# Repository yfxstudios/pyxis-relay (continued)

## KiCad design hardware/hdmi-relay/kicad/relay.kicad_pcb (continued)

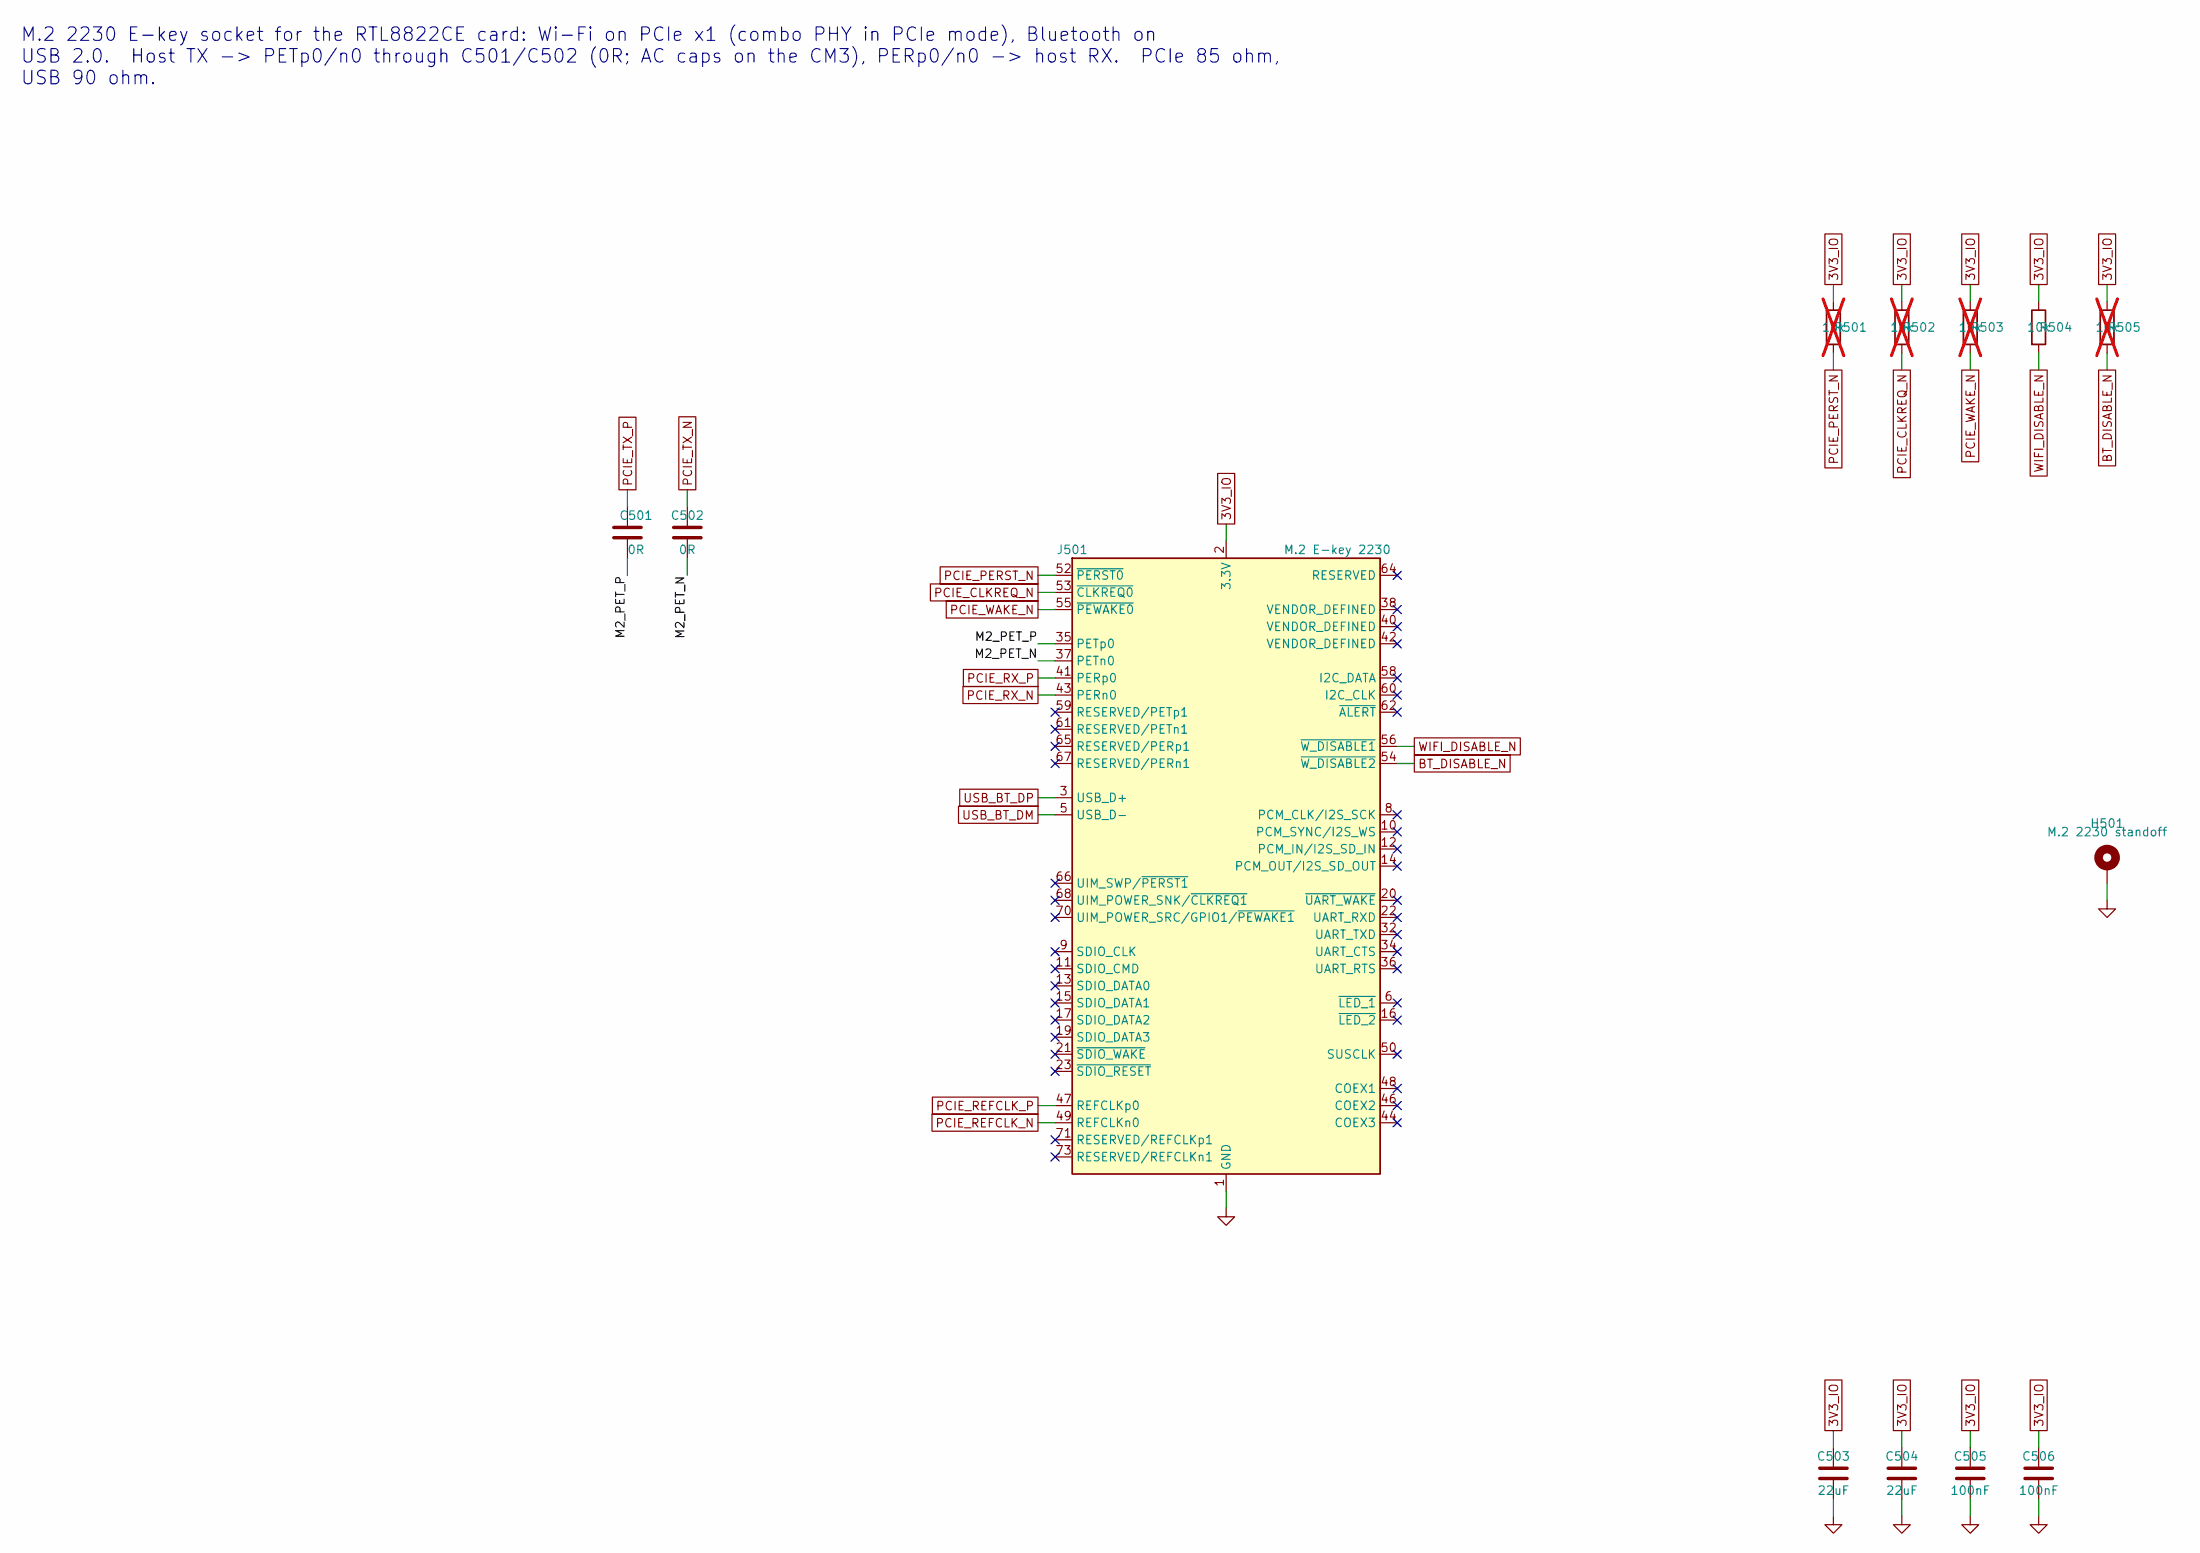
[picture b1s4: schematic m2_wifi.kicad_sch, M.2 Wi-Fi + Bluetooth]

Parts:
C501, C502: 0R; C_0402_1005Metric
C503, C504: 22uF; C_0805_2012Metric
C505, C506: 100nF; C_0402_1005Metric
H501: M.2 2230 standoff; MountingHole_2.2mm_M2_Pad_Via
J501: M.2 E-key 2230; TE_M.2_E_2x38-1MP_P0.5mm
R501, R502, R503, R505: 10k; R_0402_1005Metric; not fitted
R504: 10k; R_0402_1005Metric

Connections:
3V3_IO: C503.1, C504.1, C505.1, C506.1, J501.2 (3.3V), J501.4 (3.3V), J501.72 (3.3V), J501.74 (3.3V), R501.1, R502.1, R503.1, R504.1, R505.1; also elsewhere on the board
/M.2 Wi-Fi + Bluetooth/M2_PET_N: C502.2, J501.37 (PETn0)
/M.2 Wi-Fi + Bluetooth/M2_PET_P: C501.2, J501.35 (PETp0)
BT_DISABLE_N: J501.54 (~W_DISABLE2), R505.2; also elsewhere on the board
GND: C503.2, C504.2, C505.2, C506.2, H501.1, J501.1 (GND), J501.7 (GND), J501.18 (GND), J501.33 (GND), J501.39 (GND), J501.45 (GND), J501.51 (GND), J501.57 (GND), J501.63 (GND), J501.69 (GND), J501.75 (GND); also elsewhere on the board
PCIE_CLKREQ_N: J501.53 (~CLKREQ0), R502.2; also elsewhere on the board
PCIE_PERST_N: J501.52 (~PERST0), R501.2; also elsewhere on the board
PCIE_REFCLK_N: J501.49 (REFCLKn0); also elsewhere on the board
PCIE_REFCLK_P: J501.47 (REFCLKp0); also elsewhere on the board
PCIE_RX_N: J501.43 (PERn0); also elsewhere on the board
PCIE_RX_P: J501.41 (PERp0); also elsewhere on the board
PCIE_TX_N: C502.1; also elsewhere on the board
PCIE_TX_P: C501.1; also elsewhere on the board
PCIE_WAKE_N: J501.55 (~PEWAKE0), R503.2; also elsewhere on the board
USB_BT_DM: J501.5 (USB_D-); also elsewhere on the board
USB_BT_DP: J501.3 (USB_D+); also elsewhere on the board
WIFI_DISABLE_N: J501.56 (~W_DISABLE1), R504.2; also elsewhere on the board

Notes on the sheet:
M.2 2230 E-key socket for the RTL8822CE card: Wi-Fi on PCIe x1 (combo PHY in PCIe mode), Bluetooth on USB 2.0. Host TX -> PETp0/n0 through C501/C502 (0R; AC caps on the CM3), PERp0/n0 -> host RX. PCIe 85 ohm, USB 90 ohm.

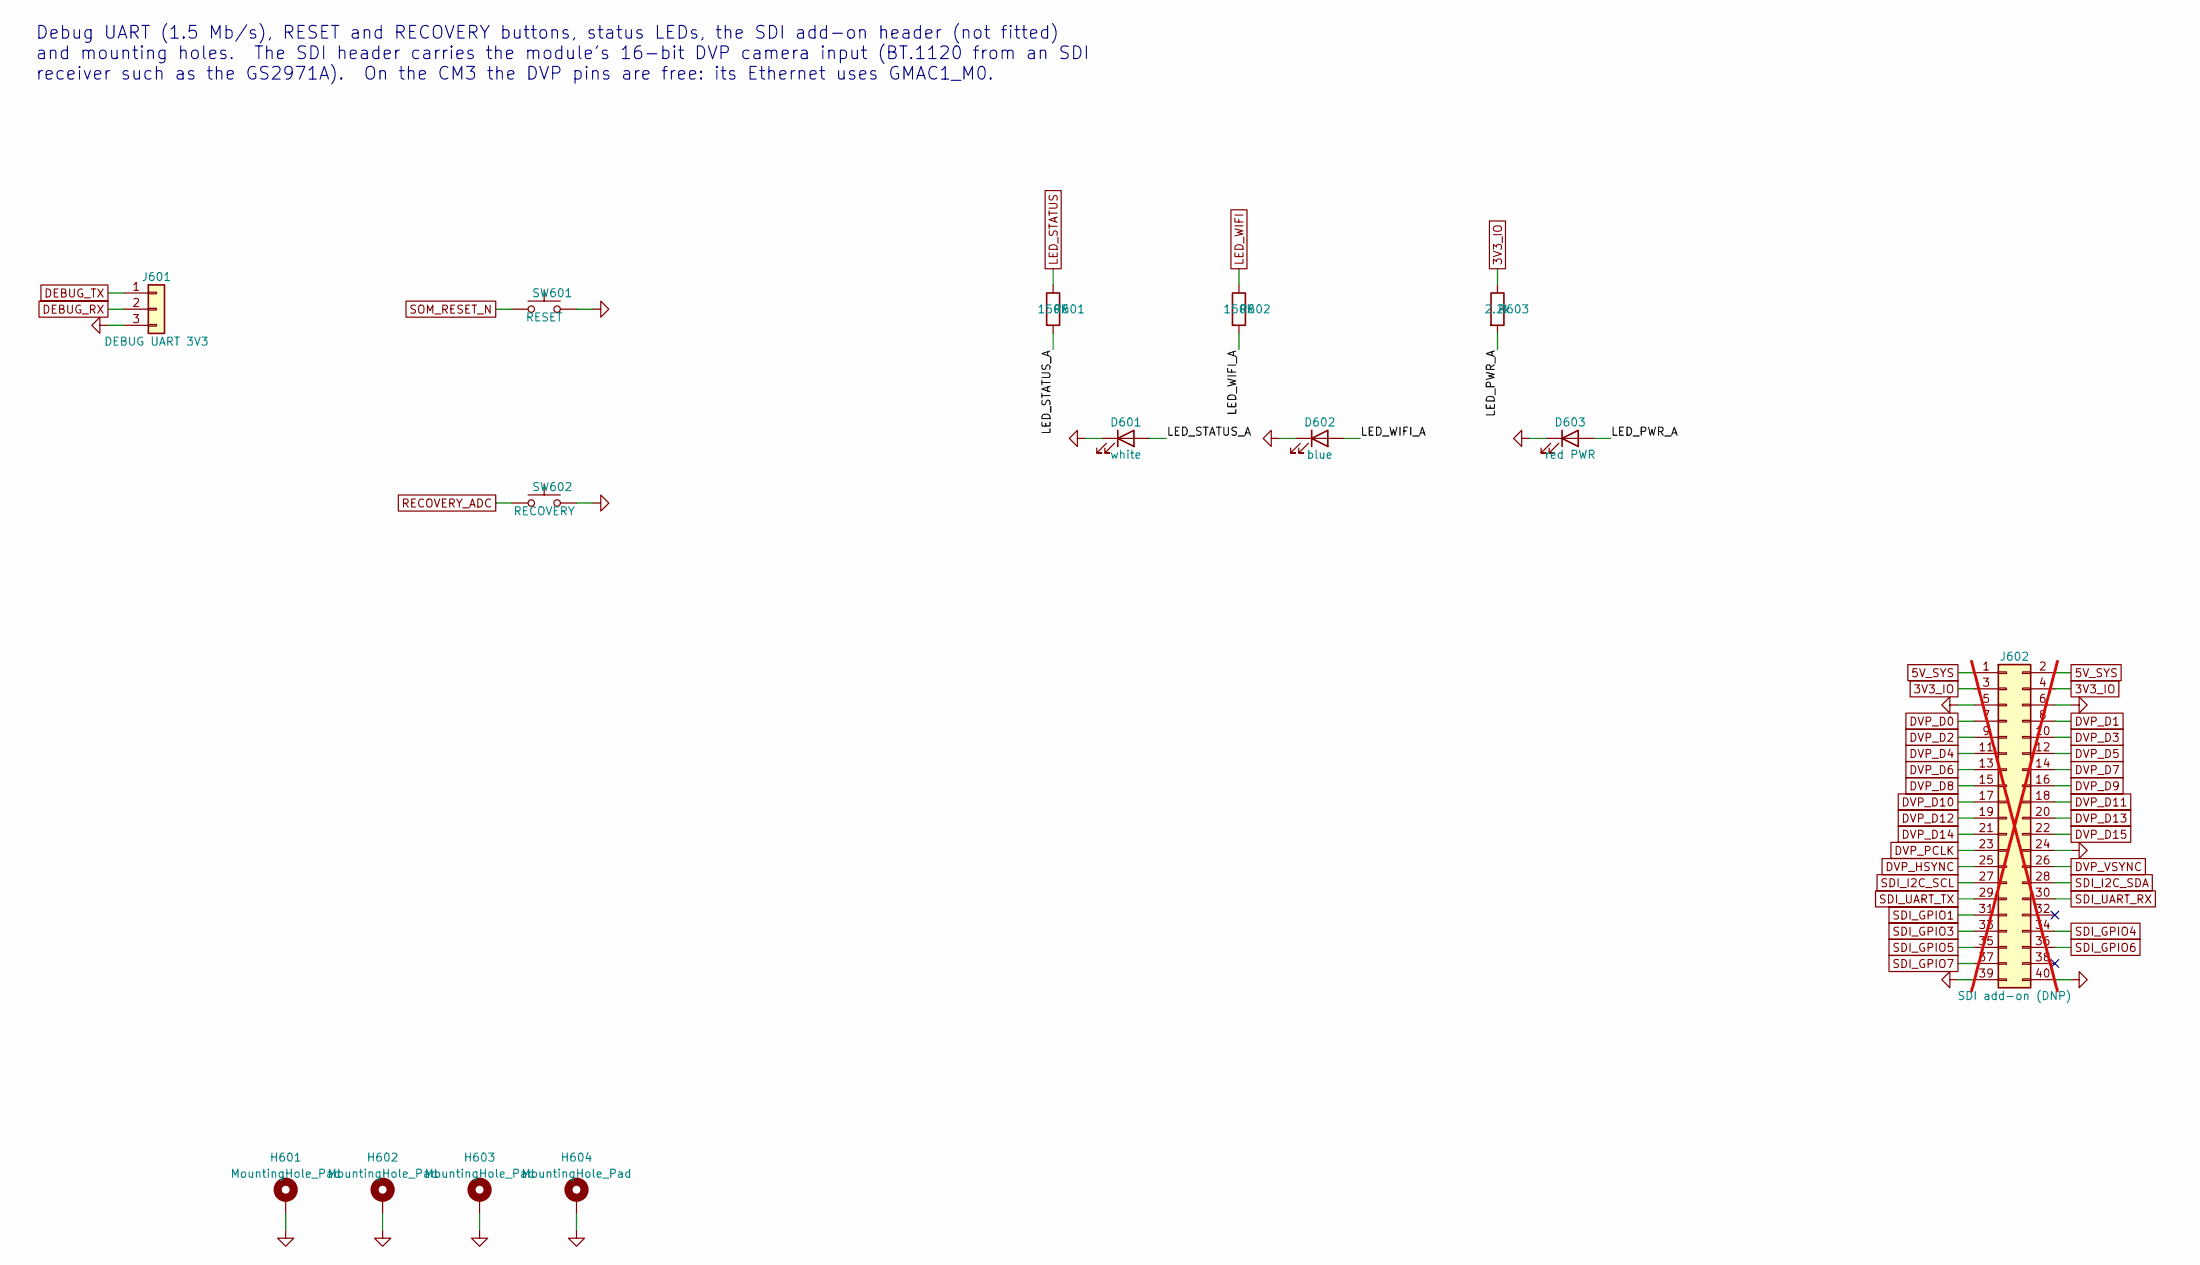
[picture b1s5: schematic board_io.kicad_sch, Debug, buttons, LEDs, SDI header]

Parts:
D601: white; LED_0603_1608Metric
D602: blue; LED_0603_1608Metric
D603: red PWR; LED_0603_1608Metric
H601, H602, H603, H604: MountingHole_Pad; MountingHole_3.2mm_M3_Pad_Via
J601: DEBUG UART 3V3; PinHeader_1x03_P2.54mm_Vertical
J602: SDI add-on (DNP); PinHeader_2x20_P2.00mm_Vertical; not fitted
R601, R602: 150R; R_0402_1005Metric
R603: 2.2k; R_0402_1005Metric
SW601: RESET; SW_SPST_TL3342
SW602: RECOVERY; SW_SPST_TL3342

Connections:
3V3_IO: J602.3, J602.4, R603.1; also elsewhere on the board
5V_SYS: J602.1, J602.2; also elsewhere on the board
/Debug, buttons, LEDs, SDI header/LED_PWR_A: D603.2 (A), R603.2
/Debug, buttons, LEDs, SDI header/LED_STATUS_A: D601.2 (A), R601.2
/Debug, buttons, LEDs, SDI header/LED_WIFI_A: D602.2 (A), R602.2
DEBUG_RX: J601.2; also elsewhere on the board
DEBUG_TX: J601.1; also elsewhere on the board
DVP_D0: J602.7; also elsewhere on the board
DVP_D1: J602.8; also elsewhere on the board
DVP_D2: J602.9; also elsewhere on the board
DVP_D3: J602.10; also elsewhere on the board
DVP_D4: J602.11; also elsewhere on the board
DVP_D5: J602.12; also elsewhere on the board
DVP_D6: J602.13; also elsewhere on the board
DVP_D7: J602.14; also elsewhere on the board
DVP_D8: J602.15; also elsewhere on the board
DVP_D9: J602.16; also elsewhere on the board
DVP_D10: J602.17; also elsewhere on the board
DVP_D11: J602.18; also elsewhere on the board
DVP_D12: J602.19; also elsewhere on the board
DVP_D13: J602.20; also elsewhere on the board
DVP_D14: J602.21; also elsewhere on the board
DVP_D15: J602.22; also elsewhere on the board
DVP_HSYNC: J602.25; also elsewhere on the board
DVP_PCLK: J602.23; also elsewhere on the board
DVP_VSYNC: J602.26; also elsewhere on the board
GND: D601.1 (K), D602.1 (K), D603.1 (K), H601.1, H602.1, H603.1, H604.1, J601.3, J602.5, J602.6, J602.24, J602.39, J602.40, SW601.2, SW602.2; also elsewhere on the board
LED_WIFI: R602.1; also elsewhere on the board
RECOVERY_ADC: SW602.1; also elsewhere on the board
SDI_GPIO1: J602.31; also elsewhere on the board
SDI_GPIO3: J602.33; also elsewhere on the board
SDI_GPIO4: J602.34; also elsewhere on the board
SDI_GPIO5: J602.35; also elsewhere on the board
SDI_GPIO6: J602.36; also elsewhere on the board
SDI_GPIO7: J602.37; also elsewhere on the board
SDI_I2C_SCL: J602.27; also elsewhere on the board
SDI_I2C_SDA: J602.28; also elsewhere on the board
SDI_UART_RX: J602.30; also elsewhere on the board
SDI_UART_TX: J602.29; also elsewhere on the board
SOM_RESET_N: SW601.1; also elsewhere on the board

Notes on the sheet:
Debug UART (1.5 Mb/s), RESET and RECOVERY buttons, status LEDs, the SDI add-on header (not fitted) and mounting holes. The SDI header carries the module's 16-bit DVP camera input (BT.1120 from an SDI receiver such as the GS2971A). On the CM3 the DVP pins are free: its Ethernet uses GMAC1_M0.

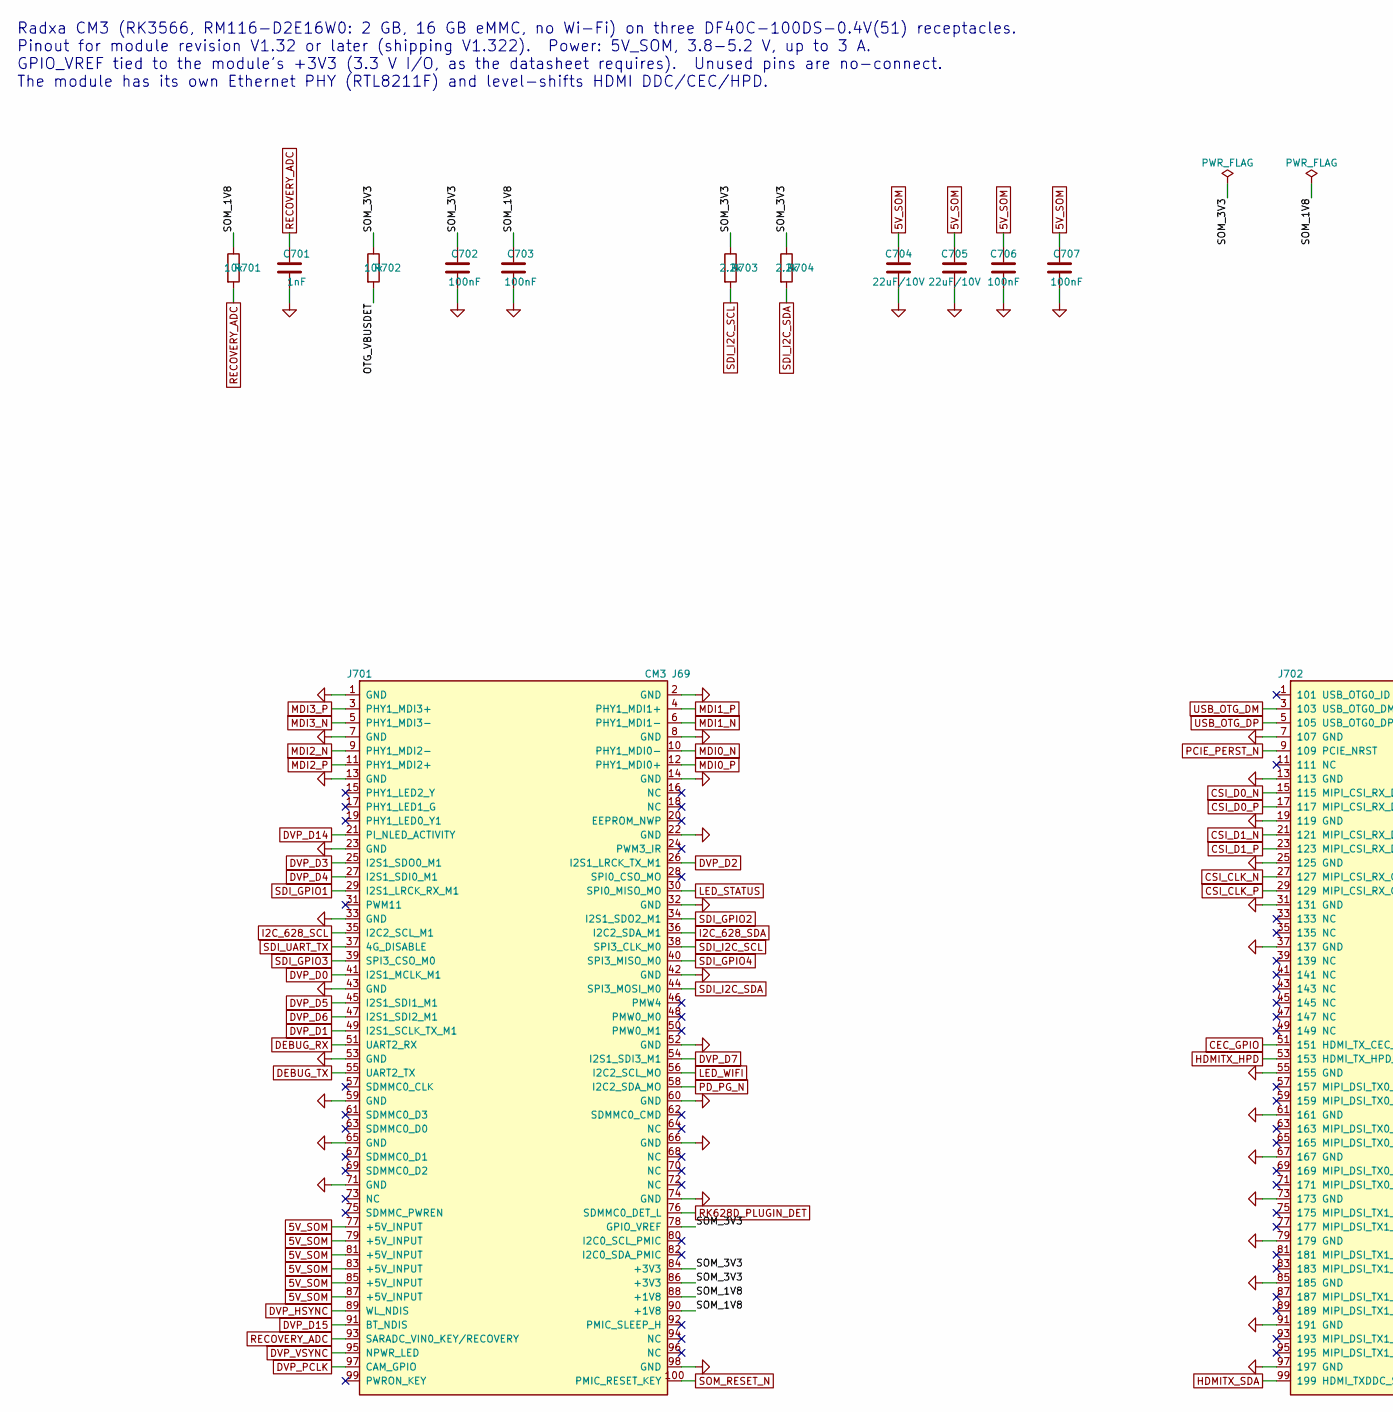
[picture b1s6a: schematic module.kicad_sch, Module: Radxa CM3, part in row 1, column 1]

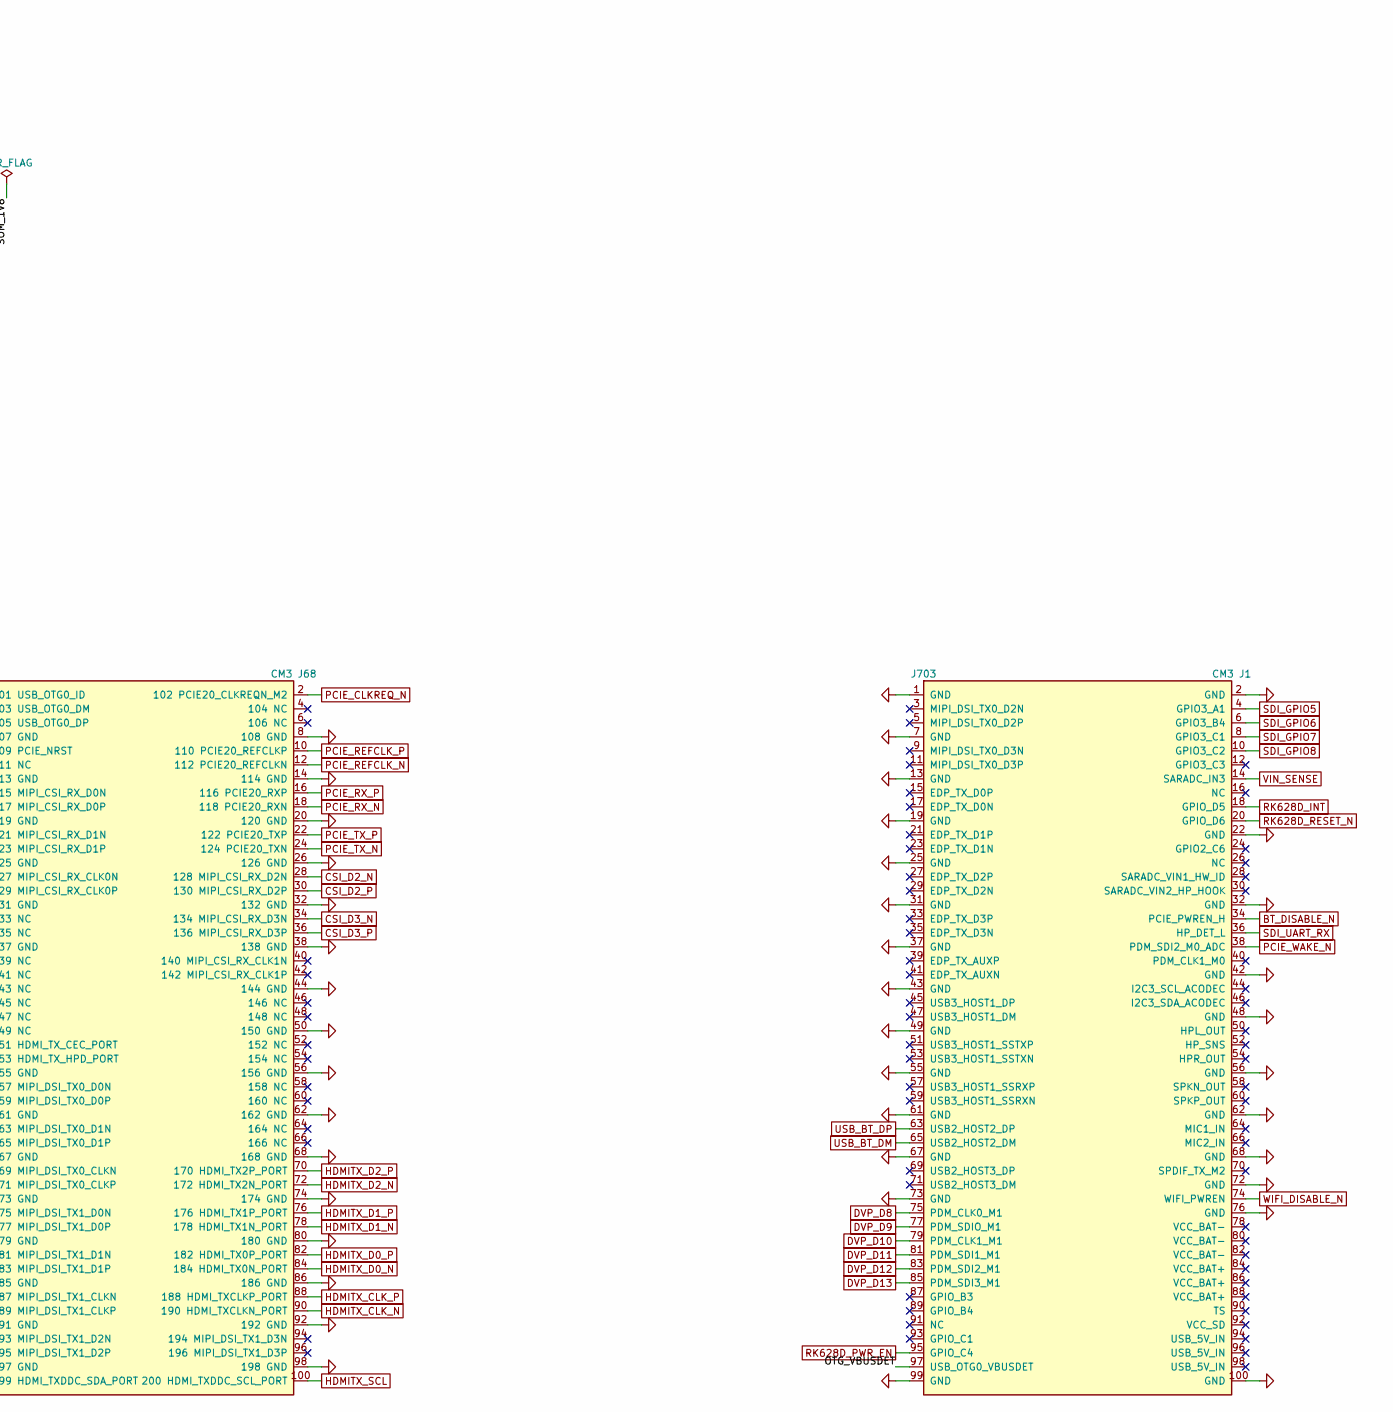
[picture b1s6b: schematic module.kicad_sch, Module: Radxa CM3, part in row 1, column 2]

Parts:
C701: 1nF; C_0402_1005Metric
C702, C703, C706, C707: 100nF; C_0402_1005Metric
C704, C705: 22uF/10V; C_0805_2012Metric
J701: CM3 J69; Radxa_CM3_J69; LCSC C597931
J702: CM3 J68; Radxa_CM3_J68; LCSC C597931
J703: CM3 J1; Radxa_CM3_J1; LCSC C597931
R701, R702: 10k; R_0402_1005Metric
R703, R704: 2.2k; R_0402_1005Metric

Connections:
5V_SOM: C704.1, C705.1, C706.1, C707.1, J701.77 (+5V_INPUT), J701.79 (+5V_INPUT), J701.81 (+5V_INPUT), J701.83 (+5V_INPUT), J701.85 (+5V_INPUT), J701.87 (+5V_INPUT); also elsewhere on the board
/Module: Radxa CM3/OTG_VBUSDET: J703.97 (USB_OTG0_VBUSDET), R702.2
/Module: Radxa CM3/SOM_1V8: C703.1, J701.88 (+1V8), J701.90 (+1V8), R701.1
/Module: Radxa CM3/SOM_3V3: C702.1, J701.78 (GPIO_VREF), J701.84 (+3V3), J701.86 (+3V3), R702.1, R703.1, R704.1
BT_DISABLE_N: J703.40 (PDM_CLK1_M0); also elsewhere on the board
CEC_GPIO: J702.51 (151 HDMI_TX_CEC_PORT); also elsewhere on the board
CSI_CLK_N: J702.27 (127 MIPI_CSI_RX_CLK0N); also elsewhere on the board
CSI_CLK_P: J702.29 (129 MIPI_CSI_RX_CLK0P); also elsewhere on the board
CSI_D0_N: J702.15 (115 MIPI_CSI_RX_D0N); also elsewhere on the board
CSI_D0_P: J702.17 (117 MIPI_CSI_RX_D0P); also elsewhere on the board
CSI_D1_N: J702.21 (121 MIPI_CSI_RX_D1N); also elsewhere on the board
CSI_D1_P: J702.23 (123 MIPI_CSI_RX_D1P); also elsewhere on the board
CSI_D2_N: J702.28 (128 MIPI_CSI_RX_D2N); also elsewhere on the board
CSI_D2_P: J702.30 (130 MIPI_CSI_RX_D2P); also elsewhere on the board
CSI_D3_N: J702.34 (134 MIPI_CSI_RX_D3N); also elsewhere on the board
CSI_D3_P: J702.36 (136 MIPI_CSI_RX_D3P); also elsewhere on the board
DEBUG_RX: J701.51 (UART2_RX); also elsewhere on the board
DEBUG_TX: J701.55 (UART2_TX); also elsewhere on the board
DVP_D0: J701.41 (I2S1_MCLK_M1); also elsewhere on the board
DVP_D1: J701.49 (I2S1_SCLK_TX_M1); also elsewhere on the board
DVP_D2: J701.26 (I2S1_LRCK_TX_M1); also elsewhere on the board
DVP_D3: J701.25 (I2S1_SDO0_M1); also elsewhere on the board
DVP_D4: J701.27 (I2S1_SDI0_M1); also elsewhere on the board
DVP_D5: J701.45 (I2S1_SDI1_M1); also elsewhere on the board
DVP_D6: J701.47 (I2S1_SDI2_M1); also elsewhere on the board
DVP_D7: J701.54 (I2S1_SDI3_M1); also elsewhere on the board
DVP_D8: J703.75 (PDM_CLK0_M1); also elsewhere on the board
DVP_D9: J703.77 (PDM_SDIO_M1); also elsewhere on the board
DVP_D10: J703.79 (PDM_CLK1_M1); also elsewhere on the board
DVP_D11: J703.81 (PDM_SDI1_M1); also elsewhere on the board
DVP_D12: J703.83 (PDM_SDI2_M1); also elsewhere on the board
DVP_D13: J703.85 (PDM_SDI3_M1); also elsewhere on the board
DVP_D14: J701.21 (PI_NLED_ACTIVITY); also elsewhere on the board
DVP_D15: J701.91 (BT_NDIS); also elsewhere on the board
DVP_HSYNC: J701.89 (WL_NDIS); also elsewhere on the board
DVP_PCLK: J701.97 (CAM_GPIO); also elsewhere on the board
DVP_VSYNC: J701.95 (NPWR_LED); also elsewhere on the board
GND: C701.2, C702.2, C703.2, C704.2, C705.2, C706.2, C707.2, J701.1 (GND), J701.2 (GND), J701.7 (GND), J701.8 (GND), J701.13 (GND), J701.14 (GND), J701.22 (GND), J701.23 (GND), J701.32 (GND), J701.33 (GND), J701.42 (GND), J701.43 (GND), J701.52 (GND), J701.53 (GND), J701.59 (GND), J701.60 (GND), J701.65 (GND), J701.66 (GND), J701.71 (GND), J701.74 (GND), J701.98 (GND), J702.7 (107 GND), J702.8 (108 GND), J702.13 (113 GND), J702.14 (114 GND), J702.19 (119 GND), J702.20 (120 GND), J702.25 (125 GND), J702.26 (126 GND), J702.31 (131 GND), J702.32 (132 GND), J702.37 (137 GND), J702.38 (138 GND), J702.44 (144 GND), J702.50 (150 GND), J702.55 (155 GND), J702.56 (156 GND), J702.61 (161 GND), J702.62 (162 GND), J702.67 (167 GND), J702.68 (168 GND), J702.73 (173 GND), J702.74 (174 GND), J702.79 (179 GND), J702.80 (180 GND), J702.85 (185 GND), J702.86 (186 GND), J702.91 (191 GND), J702.92 (192 GND), J702.97 (197 GND), J702.98 (198 GND), J703.1 (GND), J703.2 (GND), J703.7 (GND), J703.13 (GND), J703.19 (GND), J703.22 (GND), J703.25 (GND), J703.31 (GND), J703.32 (GND), J703.37 (GND), J703.42 (GND), J703.43 (GND), J703.48 (GND), J703.49 (GND), J703.55 (GND), J703.56 (GND), J703.61 (GND), J703.62 (GND), J703.67 (GND), J703.68 (GND), J703.72 (GND), J703.73 (GND), J703.76 (GND), J703.99 (GND), J703.100 (GND); also elsewhere on the board
HDMITX_CLK_N: J702.90 (190 HDMI_TXCLKN_PORT); also elsewhere on the board
HDMITX_CLK_P: J702.88 (188 HDMI_TXCLKP_PORT); also elsewhere on the board
HDMITX_D0_N: J702.84 (184 HDMI_TX0N_PORT); also elsewhere on the board
HDMITX_D0_P: J702.82 (182 HDMI_TX0P_PORT); also elsewhere on the board
HDMITX_D1_N: J702.78 (178 HDMI_TX1N_PORT); also elsewhere on the board
HDMITX_D1_P: J702.76 (176 HDMI_TX1P_PORT); also elsewhere on the board
HDMITX_D2_N: J702.72 (172 HDMI_TX2N_PORT); also elsewhere on the board
HDMITX_D2_P: J702.70 (170 HDMI_TX2P_PORT); also elsewhere on the board
HDMITX_HPD: J702.53 (153 HDMI_TX_HPD_PORT); also elsewhere on the board
HDMITX_SCL: J702.100 (200 HDMI_TXDDC_SCL_PORT); also elsewhere on the board
HDMITX_SDA: J702.99 (199 HDMI_TXDDC_SDA_PORT); also elsewhere on the board
I2C_628_SCL: J701.35 (I2C2_SCL_M1); also elsewhere on the board
I2C_628_SDA: J701.36 (I2C2_SDA_M1); also elsewhere on the board
LED_WIFI: J701.75 (SDMMC_PWREN); also elsewhere on the board
MDI0_N: J701.10 (PHY1_MDI0-); also elsewhere on the board
MDI0_P: J701.12 (PHY1_MDI0+); also elsewhere on the board
MDI1_N: J701.6 (PHY1_MDI1-); also elsewhere on the board
MDI1_P: J701.4 (PHY1_MDI1+); also elsewhere on the board
MDI2_N: J701.9 (PHY1_MDI2-); also elsewhere on the board
MDI2_P: J701.11 (PHY1_MDI2+); also elsewhere on the board
MDI3_N: J701.5 (PHY1_MDI3-); also elsewhere on the board
MDI3_P: J701.3 (PHY1_MDI3+); also elsewhere on the board
PCIE_CLKREQ_N: J702.2 (102 PCIE20_CLKREQN_M2); also elsewhere on the board
PCIE_PERST_N: J702.9 (109 PCIE_NRST); also elsewhere on the board
PCIE_REFCLK_N: J702.12 (112 PCIE20_REFCLKN); also elsewhere on the board
PCIE_REFCLK_P: J702.10 (110 PCIE20_REFCLKP); also elsewhere on the board
PCIE_RX_N: J702.18 (118 PCIE20_RXN); also elsewhere on the board
PCIE_RX_P: J702.16 (116 PCIE20_RXP); also elsewhere on the board
PCIE_TX_N: J702.24 (124 PCIE20_TXN); also elsewhere on the board
PCIE_TX_P: J702.22 (122 PCIE20_TXP); also elsewhere on the board
PCIE_WAKE_N: J703.38 (PDM_SDI2_M0_ADC); also elsewhere on the board
RECOVERY_ADC: C701.1, J701.93 (SARADC_VIN0_KEY/RECOVERY), R701.2; also elsewhere on the board
RK628D_INT: J703.12 (GPIO3_C3); also elsewhere on the board
RK628D_PLUGIN_DET: J701.76 (SDMMC0_DET_L); also elsewhere on the board
RK628D_PWR_EN: J703.95 (GPIO_C4); also elsewhere on the board
SDI_GPIO1: J701.29 (I2S1_LRCK_RX_M1); also elsewhere on the board
SDI_GPIO3: J701.39 (SPI3_CSO_M0); also elsewhere on the board
SDI_GPIO4: J701.40 (SPI3_MISO_M0); also elsewhere on the board
SDI_GPIO5: J703.4 (GPIO3_A1); also elsewhere on the board
SDI_GPIO6: J703.6 (GPIO3_B4); also elsewhere on the board
SDI_GPIO7: J703.8 (GPIO3_C1); also elsewhere on the board
SDI_I2C_SCL: J701.38 (SPI3_CLK_M0), R703.2; also elsewhere on the board
SDI_I2C_SDA: J701.44 (SPI3_MOSI_M0), R704.2; also elsewhere on the board
SDI_UART_RX: J703.36 (HP_DET_L); also elsewhere on the board
SDI_UART_TX: J701.37 (4G_DISABLE); also elsewhere on the board
SOM_RESET_N: J701.100 (PMIC_RESET_KEY); also elsewhere on the board
USB_BT_DM: J703.65 (USB2_HOST2_DM); also elsewhere on the board
USB_BT_DP: J703.63 (USB2_HOST2_DP); also elsewhere on the board
USB_OTG_DM: J702.3 (103 USB_OTG0_DM); also elsewhere on the board
USB_OTG_DP: J702.5 (105 USB_OTG0_DP); also elsewhere on the board
VIN_SENSE: J703.14 (SARADC_IN3); also elsewhere on the board
WIFI_DISABLE_N: J703.74 (WIFI_PWREN); also elsewhere on the board

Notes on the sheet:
Radxa CM3 (RK3566, RM116-D2E16W0: 2 GB, 16 GB eMMC, no Wi-Fi) on three DF40C-100DS-0.4V(51) receptacles. Pinout for module revision V1.32 or later (shipping V1.322). Power: 5V_SOM, 3.8-5.2 V, up to 3 A. GPIO_VREF tied to the module's +3V3 (3.3 V I/O, as the datasheet requires). Unused pins are no-c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
